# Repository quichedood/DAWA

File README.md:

New version here : https://github.com/quichedood/DAWA-6.1

# DAWA - Data Acquisition With Arduino
French official website project : http://dawa.panik-po.com/

DAWA is an Arduino datalogger (and laptimer) shield for your motorbike.
It records 10 times per seconds in a CSV file lots of information.

# What information is logged ?
* __Raw data acquisition__ : On Triumph bikes and many others, ECU values can be directly read (I personnaly use : RPM, SPEED, GEAR POSITION, THROTTLE and BRAKE state)
* __Environement values__ : A 9-axis sensor (BNO055) is used to store G-forces and I hope soon, roll and pitch
* __Position values__ : A UBLOX 10Hz GPS chip gets realtime coordinates
* __Infrared temperatures__ : You can plug up to 4 infrared temperature sensors (tyres or ground t° for example)
* __Analog inputs__ : You can measure up to 6 analog inputs (suspension sensors for exemple)

# Where is it logged ?
Everything is stored on a micro SD card.  
10 times per seconds, a new line is created in a CSV file. This line contains every data values separated by a semicolon.  
Current values are displayed in realtime on the OLED screen attached.

# Could it be used as a laptimer ?
YES ! Since v4 and the integration of a 10Hz GPS chip, laptimer functions are available.

# How does it work ?
I couldn't make it easier !  
Press the button start recording, press again stop recording :)  
One CSV file is created on each new record.

# What about laptimer functions
A little bit more difficult, you have to put a file named "TRACKS.CSV" on the sdcard.  
This file will contain track name and finishline coordinates, one line per track :  
`<trackname>;<finishline lat. A>;<finishline lon. A>;<finishline lat. B>;<finishline lon. B>`  
`CAROLE;489799930;25224350;489800230;25226330`  
To keep precision, latitude and longitude should be converted to integers (multiply by 10 000 000).  
When start recording the closer track is automatically chosen.

# You said Bluetooth ?
Bluetooth connection is usefull in these 2 cases :
- You just finish your track session and want to know lap times / best lap
- Before using DAWA, some parameters could be adjusted, use the bluetooth console to setup them !

I'm using "Serial Bluetooth Terminal" on Androïd. Connect and type "help" to view all available commands

# What's next  
* __Laptimer split time__ : Add split time management

# Known bugs
* __Lean angle__ : Seems easy but in fact very complicated to obtain good values without drift

# Repository Contents
* /Arduino - The .ino file you need to put in the Arduino M0
* /Documentation - Some brief explanations about this shield (french - not translated)
* /Eagle Libraries - All Eagle parts I use in my schematics
* /Eagle Sources - Eagle files of this project
* /Gerber Sources - Last Gerber files, used to produce PCB
* /Partslist - A detailed BOM list

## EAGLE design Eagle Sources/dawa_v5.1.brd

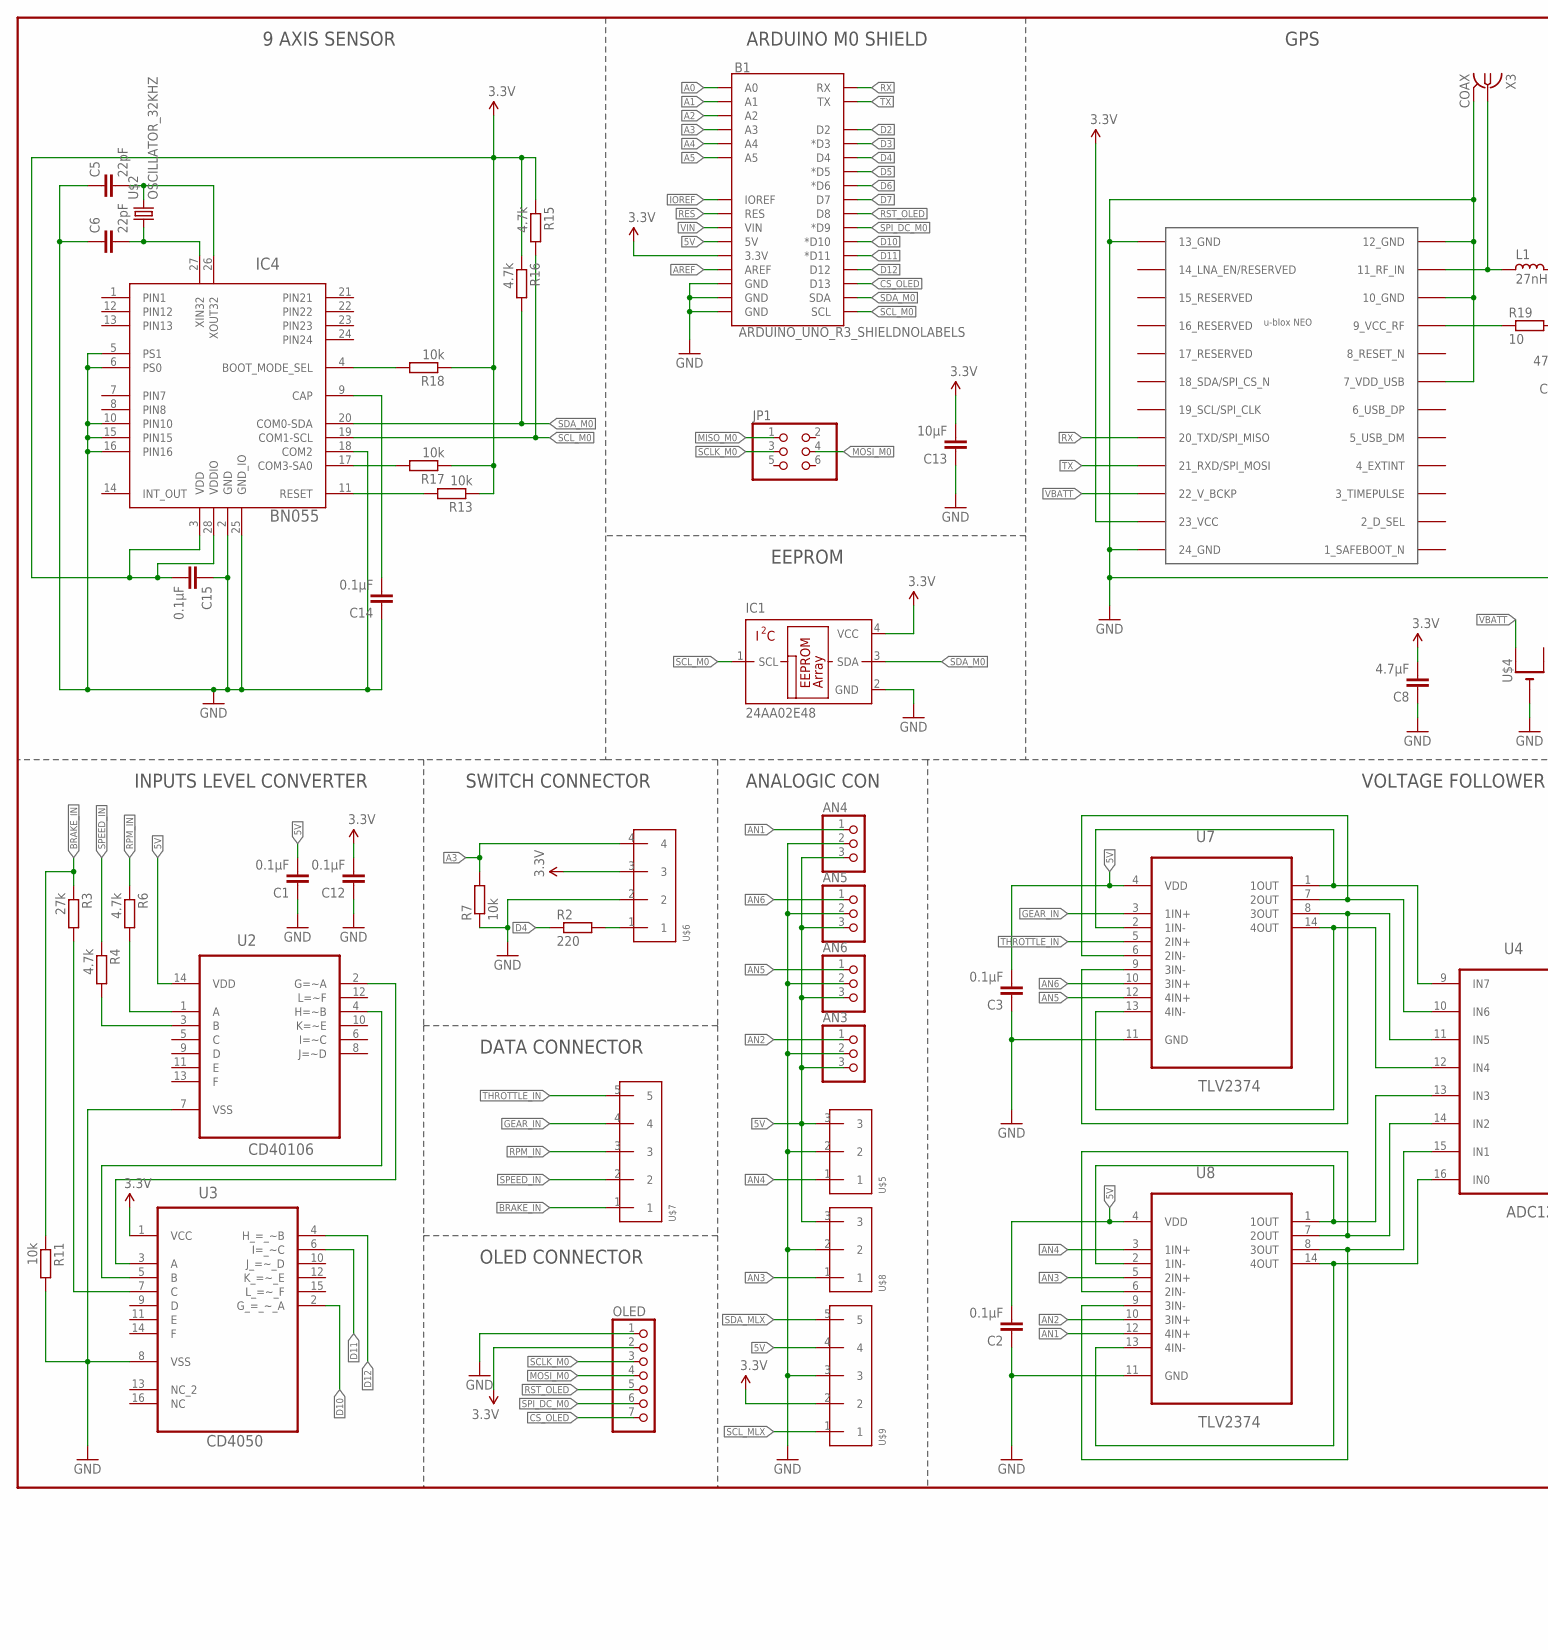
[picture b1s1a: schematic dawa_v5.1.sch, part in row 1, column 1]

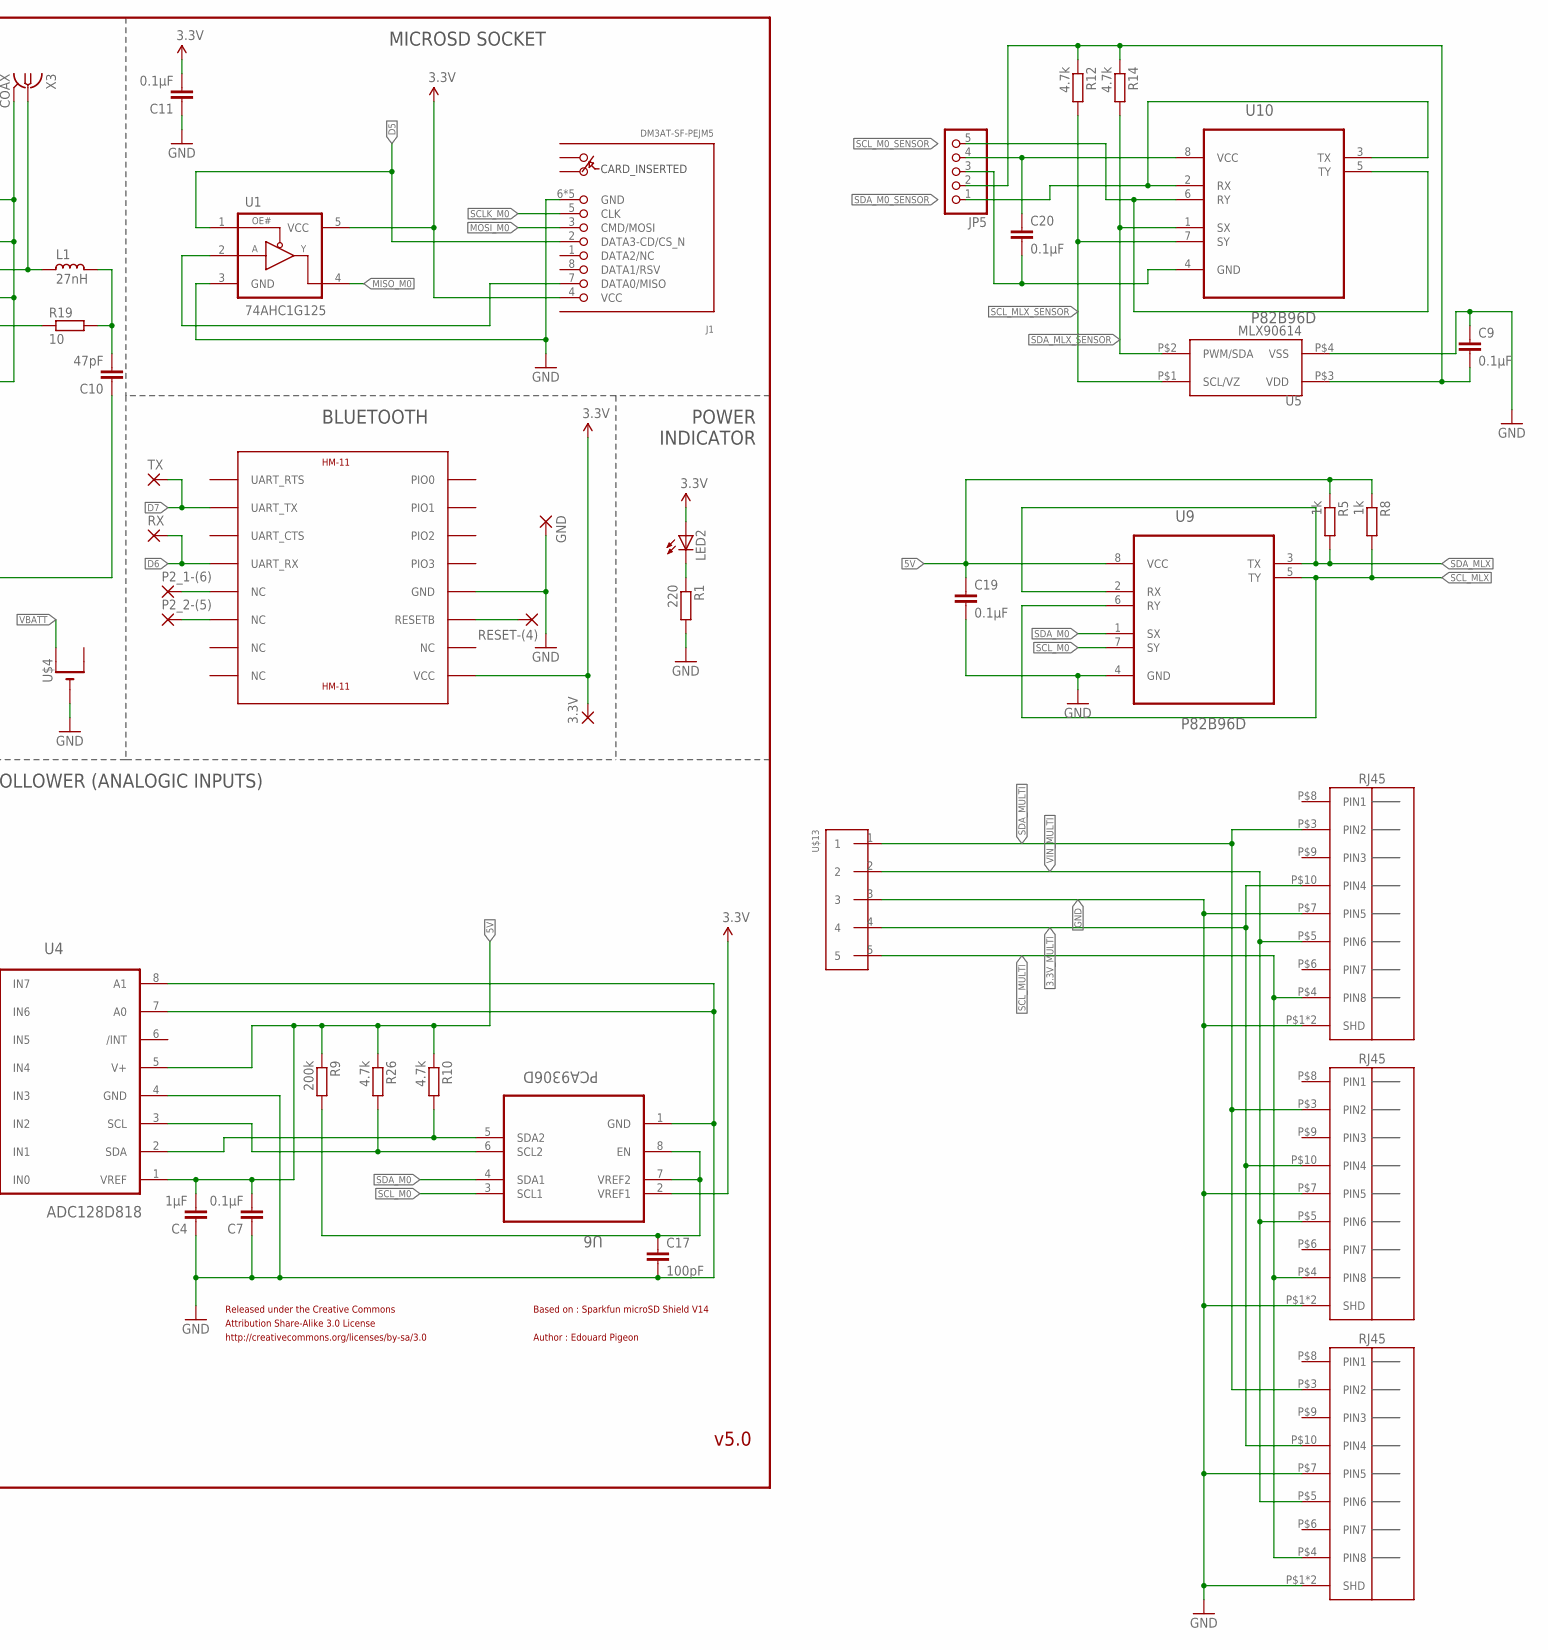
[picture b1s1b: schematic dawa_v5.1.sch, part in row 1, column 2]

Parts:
3.3V: WIREPADSMD1,27-254; SMD1,27-2,54
AN3, AN4, AN5, AN6: PINHD-1X3; 1X03
B1: ARDUINO_UNO_R3_SHIELDNOLABELS; UNO_R3_SHIELD_NOLABELS
C1, C2, C3, C7, C9, C11, C12, C14, C15, C19, C20: 0.1µF; C0603
C4: 1µF; C0603
C5, C6: 22pF; C0603
C8: 4.7µF; C0603
C10: 47pF; C0603
C13: 10µF; C0603
C17: 100pF; C0603
GND: WIREPADSMD1,27-254; SMD1,27-2,54
IC1: 24AA02E48; SOT23-5L
IC4: BN055; LGA-28_3.80X5.20/0.5
J1: DM3AT-SF-PEJM5
JP1: PINHD-2X3; 2X03
JP5: PINHD-1X5; 1X05
L1: 27nH; L0603
LED2: LEDCHIPLED_1206; CHIPLED_1206
OLED: PINHD-1X7; 1X07
P2_1-(6), P2_2-(5): WIREPADSMD1,27-254; SMD1,27-2,54
R1, R2: 220; R0603
R3: 27k; R0603
R4, R6, R10, R12, R14, R15, R16, R26: 4.7k; R0603
R5, R8: 1k; R0603
R7, R11, R13, R17, R18: 10k; R0603
R9: 200k; R0603
R19: 10; M1206
RESET-(4): WIREPADSMD1,27-254; SMD1,27-2,54
RX: WIREPADSMD1,27-254; SMD1,27-2,54
TX: WIREPADSMD1,27-254; SMD1,27-2,54
U1: 74AHC1G125; SOT23-5
U2: CD40106; SOP65P640X120-14N
U3: CD4050; SOP65P640X120-16N
U4: ADC128D818; SOP65P640X120-16N
U5: MLX90614; TO-39
U6: PCA9306D; SOP50P310X90-8N
U7, U8: TLV2374; SOP65P640X120-14N
U9, U10: P82B96D; SOIC127P600X175-8N
U$1: HM-11
U$2: OSCILLATOR_32KHZ; OSCILLATOR_SMD
U$3: NEO-M8
U$4: CR1220SMT; CR1220-SMD
U$5, U$8: 3_PIN_JST-XH-SMD
U$6: 4_PIN_JST-XH-SMD
U$7, U$9, U$13: 5_PIN_JST-XH-SMD
U$10, U$11, U$12: RJ45
X3: COAX; MMCX-J-P-X-ST-EM1-MKT

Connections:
3.3V: 3.3V.1, B1.3.3V, C8.2, C11.2, C12.2, C13.2, C15.2, IC1.4 (VCC), IC4.3 (VDD), IC4.28 (VDDIO), J1.4 (VCC), LED2.A, OLED.2, R13.1, R15.1, R16.1, R17.1, R18.1, U1.5 (VCC), U3.1 (VCC), U6.2 (VREF1), U$1.VCC, U$3.23 (23_VCC), U$6.3, U$9.2
3.3V_MULTI: U$10.P$10 (PIN4), U$11.P$10 (PIN4), U$12.P$10 (PIN4), U$13.4
5V: AN3.3, AN4.3, AN5.3, AN6.3, B1.5V, C1.2, C2.2, C3.2, C4.2, C7.2, C19.1, R5.1, R8.1, R9.1, R10.1, R26.1, U2.14 (VDD), U4.1 (VREF), U4.5 (V+), U7.4 (VDD), U8.4 (VDD), U9.8 (VCC), U$5.3, U$8.3, U$9.4
A0: B1.A0
A1: B1.A1
A2: B1.A2
A3: B1.A3, R7.2, U$6.4
A4: B1.A4
A5: B1.A5
AN1: AN4.1, U8.12 (4IN+)
AN2: AN3.1, U8.10 (3IN+)
AN3: U8.5 (2IN+), U$8.1
AN4: U8.3 (1IN+), U$5.1
AN5: AN6.1, U7.12 (4IN+)
AN6: AN5.1, U7.10 (3IN+)
AREF: B1.AREF
BRAKE_IN: R3.1, R11.1, U$7.1
CS_OLED: B1.D13, OLED.7
D2: B1.D2
D3: B1.D3 (*D3)
D4: B1.D4, R2.1
D5: B1.D5 (*D5), J1.2 (DATA3-CD/CS_N), U1.1 (OE#)
D6: B1.D6 (*D6), RX.1, U$1.UART_RX
D7: B1.D7, TX.1, U$1.UART_TX
D10: B1.D10 (*D10), U3.2 (G_=_~_A)
D11: B1.D11 (*D11), U3.6 (I=_~C)
D12: B1.D12, U3.4 (H_=_~B)
GEAR_IN: U7.3 (1IN+), U$7.4
GND: AN3.2, AN4.2, AN5.2, AN6.2, B1.GND@0 (GND), B1.GND@1 (GND), B1.GND@2 (GND), C1.1, C2.1, C3.1, C4.1, C5.1, C6.1, C7.1, C8.1, C9.1, C10.1, C11.1, C12.1, C13.1, C14.1, C15.1, C17.2, C19.2, GND.1, IC1.2 (GND), IC4.2 (GND), IC4.5 (PS1), IC4.6 (PS0), IC4.10 (PIN10), IC4.15 (PIN15), IC4.16 (PIN16), IC4.18 (COM2), IC4.25 (GND_IO), J1.6 (GND), J1.MOUNT0 (GND), J1.MOUNT1 (GND), J1.MOUNT2 (GND), J1.MOUNT3 (GND), OLED.1, R1.2, R7.1, R11.2, U1.3 (GND), U2.7 (VSS), U3.8 (VSS), U4.4 (GND), U4.7 (A0), U4.8 (A1), U5.P$4 (VSS), U6.1 (GND), U7.11 (GND), U8.11 (GND), U9.4 (GND), U$1.GND, U$3.7 (7_VDD_USB), U$3.10 (10_GND), U$3.12 (12_GND), U$3.13 (13_GND), U$3.24 (24_GND), U$4.-, U$5.2, U$6.2, U$8.2, U$9.3, U$10.P$1 (SHD), U$10.P$2 (SHD), U$10.P$7 (PIN5), U$11.P$1 (SHD), U$11.P$2 (SHD), U$11.P$7 (PIN5), U$12.P$1 (SHD), U$12.P$2 (SHD), U$12.P$7 (PIN5), U$13.3, X3.2@1 (GND), X3.2@2 (GND), X3.2@3 (GND), X3.2@4 (GND)
IOREF: B1.IOREF
MISO_M0: JP1.1, U1.4 (Y)
MOSI_M0: J1.3 (CMD/MOSI), JP1.4, OLED.4
unnamed: R2.2, U$6.1
unnamed: R6.2, U2.1 (A)
unnamed: U2.2 (G=~A), U3.3 (A)
unnamed: R4.2, U2.3 (B)
unnamed: R3.2, U3.7 (C)
unnamed: LED2.C, R1.1
unnamed: IC4.11 (RESET), R13.2
unnamed: P2_1-(6).1, U$1.NC@5 (NC)
unnamed: RESET-(4).1, U$1.RESETB
unnamed: J1.7 (DATA0/MISO), U1.2 (A)
unnamed: C10.2, L1.1, R19.2
unnamed: U4.13 (IN3), U8.1 (1OUT), U8.2 (1IN-)
unnamed: C14.2, IC4.9 (CAP)
unnamed: IC4.4 (BOOT_MODE_SEL), R18.2
unnamed: C5.2, IC4.26 (XOUT32), U$2.2
unnamed: C6.2, IC4.27 (XIN32), U$2.1
unnamed: IC4.17 (COM3-SA0), R17.2
unnamed: P2_2-(5).1, U$1.NC@6 (NC)
unnamed: R19.1, U$3.9 (9_VCC_RF)
unnamed: L1.2, U$3.11 (11_RF_IN), X3.1
unnamed: U2.4 (H=~B), U3.5 (B)
unnamed: R26.2, U4.3 (SCL), U6.6 (SCL2)
unnamed: R10.2, U4.2 (SDA), U6.5 (SDA2)
unnamed: U4.9 (IN7), U7.1 (1OUT), U7.2 (1IN-)
unnamed: U4.10 (IN6), U7.6 (2IN-), U7.7 (2OUT)
unnamed: U4.11 (IN5), U7.8 (3OUT), U7.9 (3IN-)
unnamed: U4.12 (IN4), U7.13 (4IN-), U7.14 (4OUT)
unnamed: C17.1, R9.2, U6.7 (VREF2), U6.8 (EN)
unnamed: U4.14 (IN2), U8.6 (2IN-), U8.7 (2OUT)
unnamed: U4.15 (IN1), U8.8 (3OUT), U8.9 (3IN-)
unnamed: U4.16 (IN0), U8.13 (4IN-), U8.14 (4OUT)
unnamed: C20.1, JP5.4, U10.8 (VCC)
unnamed: C9.2, JP5.2, R12.1, R14.1, U5.P$3 (VDD)
unnamed: C20.2, JP5.3, U10.4 (GND)
RES: B1.RES
RPM_IN: R6.1, U$7.3
RST_OLED: B1.D8, OLED.5
RX: B1.RX, U$3.20 (20_TXD/SPI_MISO)
SCLK_M0: J1.5 (CLK), JP1.3, OLED.3
SCL_M0: B1.SCL, IC1.1 (SCL), IC4.19 (COM1-SCL), R15.2, U6.3 (SCL1), U9.7 (SY)
SCL_M0_SENSOR: JP5.5, U10.5 (TY), U10.6 (RY)
SCL_MLX: R8.2, U9.5 (TY), U9.6 (RY), U$9.1
SCL_MLX_SENSOR: R12.2, U5.P$1 (SCL/VZ), U10.7 (SY)
SCL_MULTI: U$10.P$4 (PIN8), U$11.P$4 (PIN8), U$12.P$4 (PIN8), U$13.5
SDA_M0: B1.SDA, IC1.3 (SDA), IC4.20 (COM0-SDA), R16.2, U6.4 (SDA1), U9.1 (SX)
SDA_M0_SENSOR: JP5.1, U10.2 (RX), U10.3 (TX)
SDA_MLX: R5.2, U9.2 (RX), U9.3 (TX), U$9.5
SDA_MLX_SENSOR: R14.2, U5.P$2 (PWM/SDA), U10.1 (SX)
SDA_MULTI: U$10.P$3 (PIN2), U$11.P$3 (PIN2), U$12.P$3 (PIN2), U$13.1
SPEED_IN: R4.1, U$7.2
SPI_DC_M0: B1.D9 (*D9), OLED.6
THROTTLE_IN: U7.5 (2IN+), U$7.5
TX: B1.TX, U$3.21 (21_RXD/SPI_MOSI)
VBATT: U$3.22 (22_V_BCKP), U$4.+$1 (+)
VIN: B1.VIN
VIN_MULTI: U$10.P$5 (PIN6), U$11.P$5 (PIN6), U$12.P$5 (PIN6), U$13.2

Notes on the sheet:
POWER INDICATOR
Released under the Creative Commons
v5.0
VOLTAGE FOLLOWER (ANALOGIC INPUTS)
MICROSD SOCKET
ARDUINO M0 SHIELD
BLUETOOTH
Attribution Share-Alike 3.0 License
http://creativecommons.org/licenses/by-sa/3.0
Based on : Sparkfun microSD Shield V14
Author : Edouard Pigeon
9 AXIS SENSOR
INPUTS LEVEL CONVERTER
OLED CONNECTOR
DATA CONNECTOR
EEPROM
SWITCH CONNECTOR
GPS
ANALOGIC CON

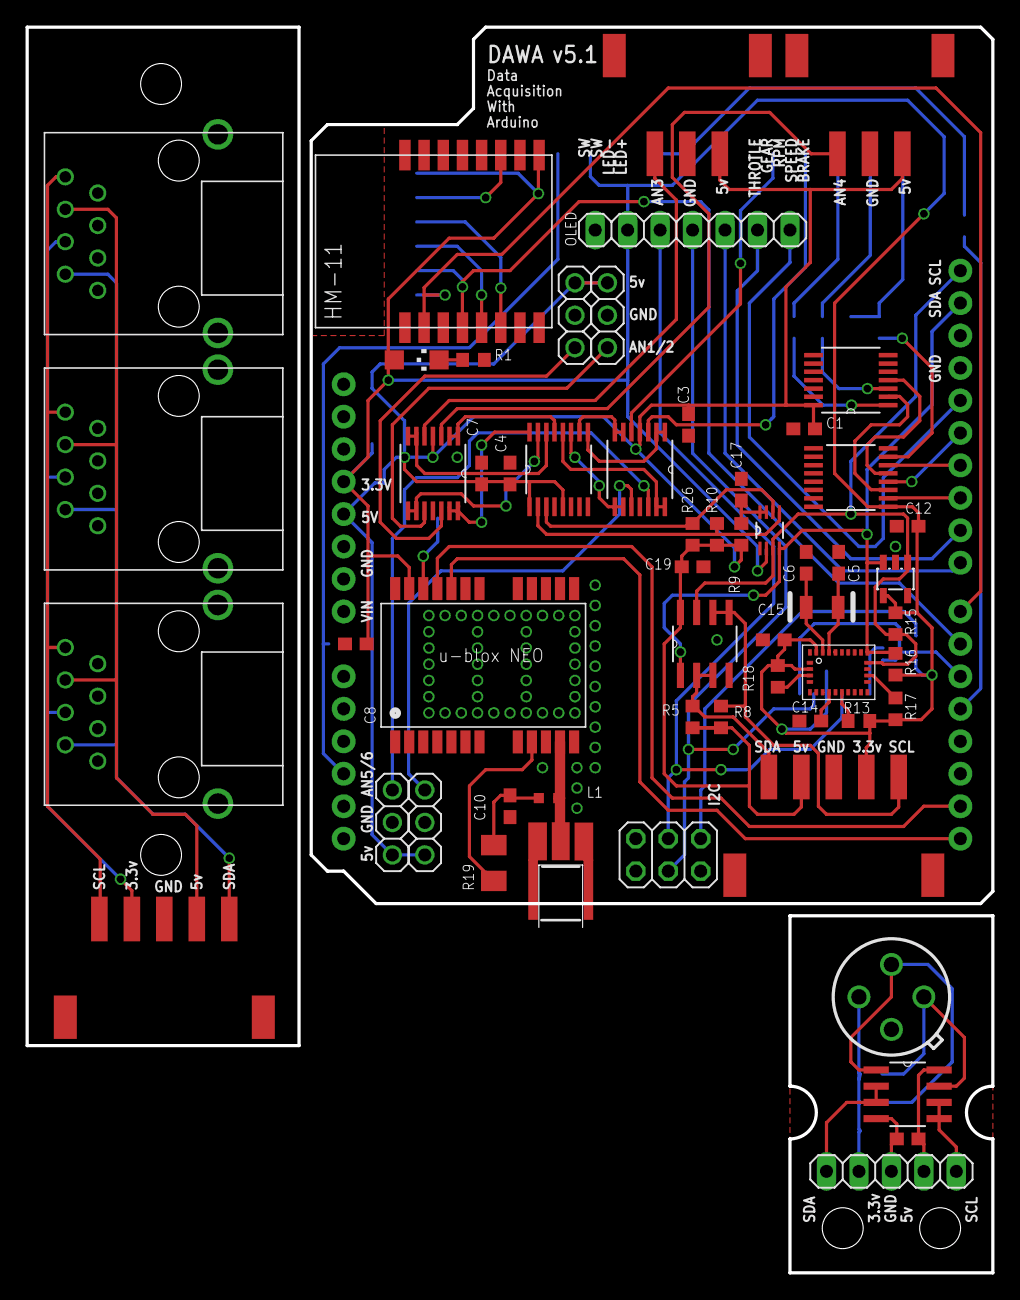
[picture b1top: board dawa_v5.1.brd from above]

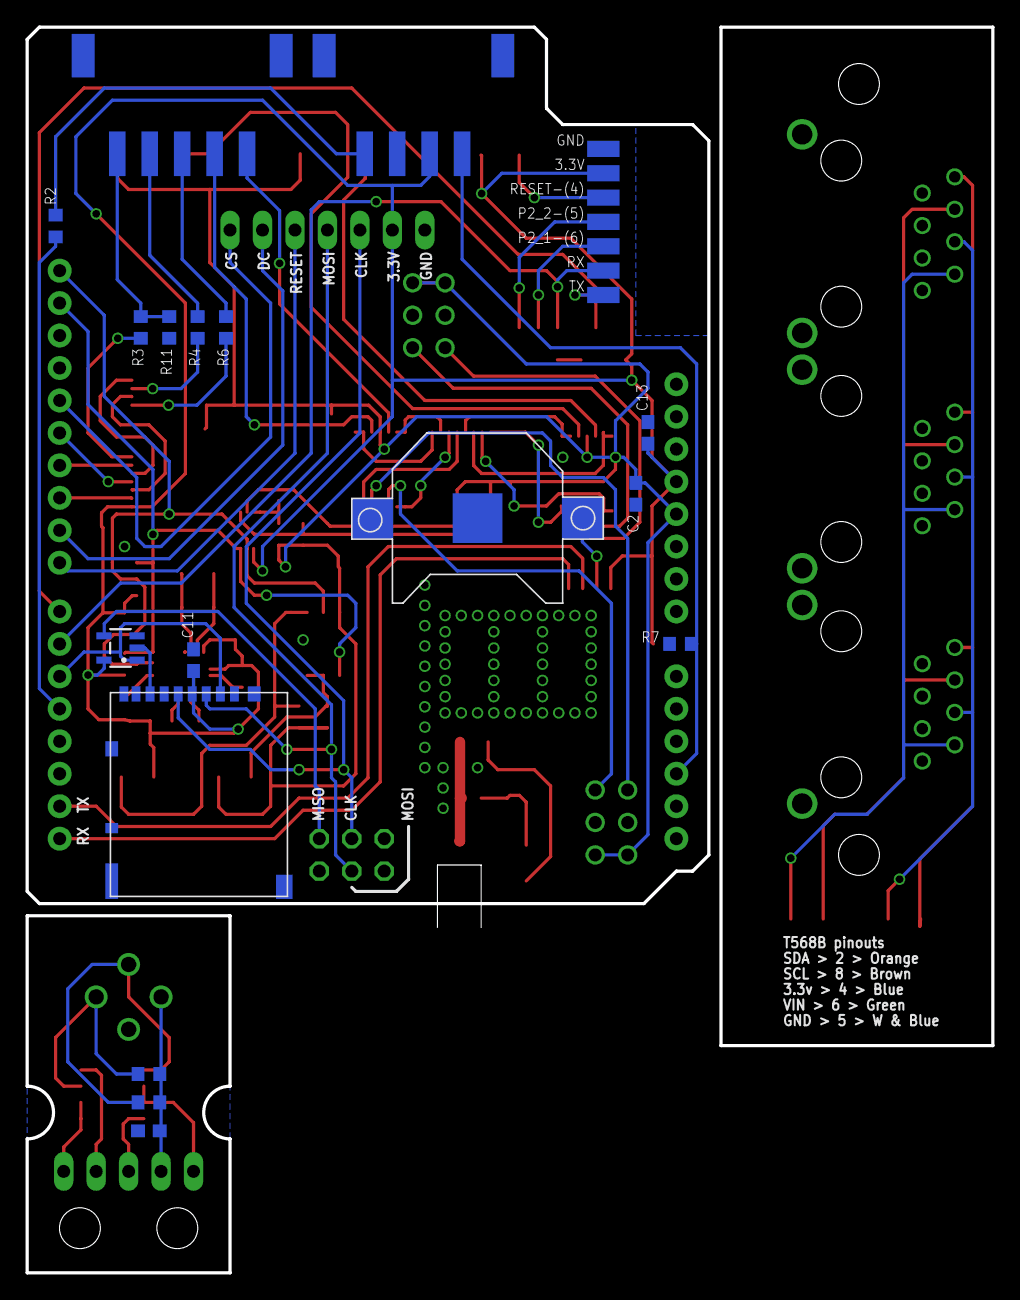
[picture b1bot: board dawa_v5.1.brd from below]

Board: 2 copper layers, 75.6 x 97.5 mm, 82 parts (24 on the bottom side), 77 nets.

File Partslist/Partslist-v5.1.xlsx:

Qty | Retailer | Value | Ref | Device | Package
1 | Mouser |  | CR1220 | 12mm 3V lithium coin cell
1 | Aliexpress |  |  | 12v connector
1 | Mouser |  | ADC128D818 | ADC | SOP65P640X120-16N
1 | Aliexpress |  |  | Arduino M0 (Robodyn)
1 | Aliexpress | 100pF |  | Capacitor | 0603
1 | Aliexpress | 10µF |  | Capacitor | 0603
1 | Aliexpress | 1µF |  | Capacitor | 0603
1 | Aliexpress | 4.7µF |  | Capacitor | 0603
2 | Aliexpress | 22pF |  | Capacitor | 0603
11 | Aliexpress | 0.1µF |  | Capacitor | 0603
1 | Mouser | 47pF | GRM1885C1H470JA01D | Capacitor | 0603
1 | Aliexpress |  | CD4050 | CMOS Hex Buffer/Converters | SOP65P640X120-16N
3 | Aliexpress |  | P82B96D | DUAL BIDIRECTIONAL BUS BUFFER | SOIC127P600X175-8N
1 | Aliexpress |  |  | GPS Antenna
1 | Aliexpress |  |  | GPS connector | MMCX STRAIGHT, EDGE MOUNT JACK- 50 OHM
1 | Aliexpress |  | UBLOX NEO-7M | GPS module
1 | Aliexpress |  |  | HM-11 (Bluetooth module) | JNHuaMao HM-11 Bluetooth 4.0 Transceiver
1 | Mouser | 27nH | LQG18HN27NJ00D | Inductor | 0603
2 | Aliexpress |  | MLX90614 ESF-BCC | Infrared temp. Sensor
1 | Mouser |  | BN055 | Intelligent 9-axis absolute orientation sensor | LGA-28_3.80X5.20/0.5
2 | Aliexpress |  |  | JST XH Connector (3 pins/F)
1 | Aliexpress |  |  | JST XH Connector (4 pins/F)
3 | Aliexpress |  |  | JST XH Connector (5 pins/F)
2 | Aliexpress |  |  | JST XH Connector (SMD/3 pins/M)
1 | Aliexpress |  |  | JST XH Connector (SMD/4 pins/M)
3 | Aliexpress |  |  | JST XH Connector (SMD/5 pins/M)
1 | Aliexpress |  |  | LED | 1206
1 | Aliexpress |  |  | Lithium coin cell 3v
1 | Aliexpress |  | DM3AT-SF-PEJM5 | Micro SD connector (SMD/push/push) | DM3AT-SF-PEJM5
1 | Aliexpress |  |  | OLED screen
2 | Mouser |  | TLV2374IPWR | OPERATIONAL AMPLIFIERS | SOP65P640X120-14N
1 | Mouser | 32.768kHz | CM7V-T1A | OSCILLATOR
1 | N/A |  |  | PCB
1 | Aliexpress |  |  | Pin header 1X32 (M)
1 | Mouser |  |  | Pin header 1X7 (F)
1 | Aliexpress |  |  | Pin header 2X3 (F)
1 | Aliexpress |  |  | Power button
1 | Mouser |  | CD40106BPW | QUADRUPLE LEVEL SHIFTER | SOP65P640X120-14N
1 | Aliexpress | 1kohm |  | Resistor | 0603
1 | Aliexpress | 200kohm |  | Resistor | 0603
1 | Aliexpress | 27kohm |  | Resistor | 0603
2 | Aliexpress | 220ohm |  | Resistor | 0603
8 | Aliexpress | 4.7kohm |  | Resistor | 0603
5 | Aliexpress | 10kohm |  | Resistor | 0603
1 | Mouser | 10ohm |  | Resistor | 1206
2 | Amazon |  |  | RJ45 (1m/2m)
3 | Aliexpress |  |  | RJ45 female socket
1 | Mouser |  | 24AA02E48 | Serial EEPROM | SOT23-5L
1 | Mouser |  | 74AHC1G125 | TRI-STATE SINGLE BUSS BUFFER | SOT23-5
1 | Mouser |  | PCA9306D | VOLTAGE-LEVEL TRANSLATOR | SOP50P310X90-8N
2 | Aliexpress |  |  | Wire cable (2m) - 4 cores
2 | Aliexpress |  |  | Wire cable (2m) - 5 cores

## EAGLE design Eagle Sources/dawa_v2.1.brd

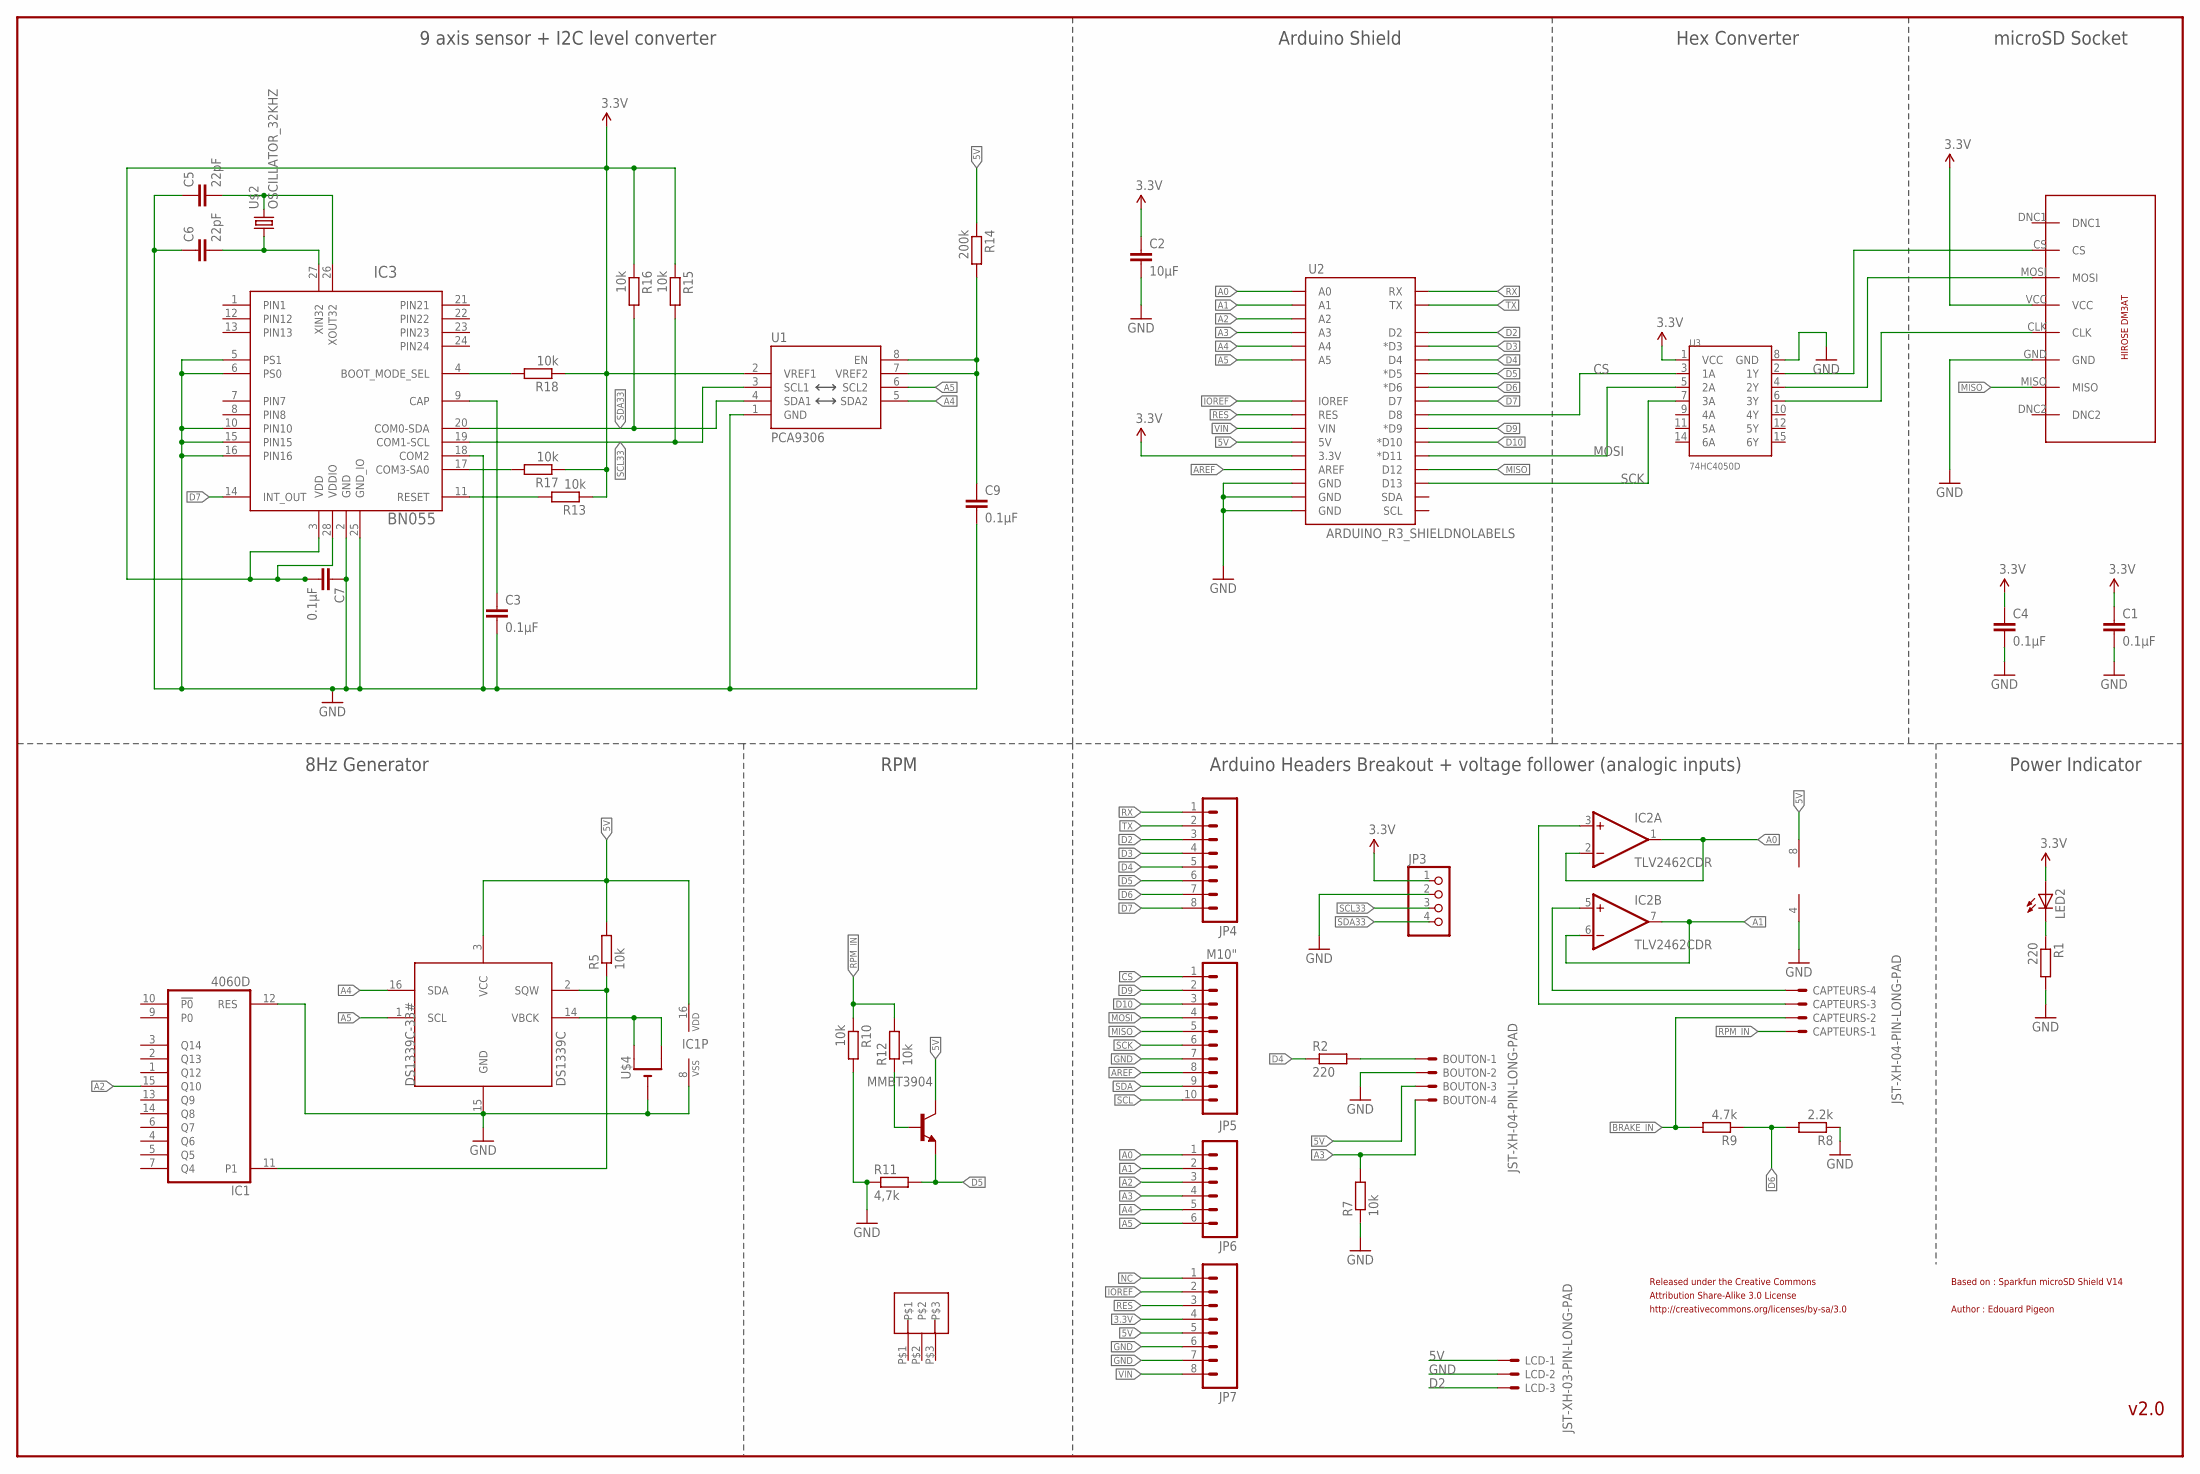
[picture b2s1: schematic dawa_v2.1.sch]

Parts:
BOUTON: JST-XH-04-PIN-LONG-PAD; JST-XH-04-PACKAGE-LONG-PAD
C1, C3, C4, C7, C9: 0.1µF; C1206
C2: 10µF; C1206
C5, C6: 22pF; C1206
CAPTEURS: JST-XH-04-PIN-LONG-PAD; JST-XH-04-PACKAGE-LONG-PAD
DS1339C-33#: DS1339C
IC1: 4060D; SO16
IC2: TLV2462CDR; SO08
IC3: BN055; LGA-28_3.80X5.20/0.5
JP3: PINHD-1X4; 1X04
JP4: M08; 1X08
JP5: M10"; 1X10
JP6: M06SIP; 1X06
JP7: M081X08; 1X08
LCD: JST-XH-03-PIN-LONG-PAD; JST-XH-03-PACKAGE-LONG-PAD
LED2: LEDCHIPLED_1206; CHIPLED_1206
MMBT3904: MMBT3904LT1-NPN-SOT23-BEC; SOT23-BEC
R1, R2: 220; M1206
R5, R7, R10, R12, R13, R15, R16, R17, R18: 10k; M1206
R8: 2.2k; M1206
R9: 4.7k; M1206
R11: 4,7k; M1206
R14: 200k; M1206
U1: PCA9306; PSOP-8
U2: ARDUINO_R3_SHIELDNOLABELS; UNO_R3_SHIELD_NOLABELS
U3: 74HC4050D; SO016
U$2: OSCILLATOR_32KHZ; OSCILLATOR_SMD
U$3: 3_PIN_JST-XH
U$4: CR1220SMT; CR1220-SMD
U$5: DM3AT

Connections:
3.3V: C1.1, C2.1, C4.1, C7.2, IC3.3 (VDD), IC3.28 (VDDIO), JP3.1, JP7.4, LED2.A, R13.1, R15.1, R16.1, R17.1, R18.1, U1.2 (VREF1), U2.3.3V, U3.1 (VCC), U$5.VCC
5V: BOUTON.3, DS1339C-33#.3 (VCC), IC1.16 (VDD), IC2.8 (V+), JP7.5, LCD.1, MMBT3904.C, R5.2, R14.1, U2.5V
A0: IC2.1 (OUT), IC2.2 (-IN), JP6.1, U2.A0
A1: IC2.6 (-IN), IC2.7 (OUT), JP6.2, U2.A1
A2: IC1.15 (Q10), JP6.3, U2.A2
A3: BOUTON.4, JP6.4, R7.2, U2.A3
A4: DS1339C-33#.16 (SDA), JP6.5, U1.5 (SDA2), U2.A4
A5: DS1339C-33#.1 (SCL), JP6.6, U1.6 (SCL2), U2.A5
AREF: JP5.8, U2.AREF
BRAKE_IN: CAPTEURS.2, R9.2
CS: JP5.1, U2.D8, U3.3 (1A)
D2: JP4.3, LCD.3, U2.D2
D3: JP4.4, U2.D3 (*D3)
D4: JP4.5, R2.1, U2.D4
D5: JP4.6, MMBT3904.E, R11.2, U2.D5 (*D5)
D6: JP4.7, R8.2, R9.1, U2.D6 (*D6)
D7: IC3.14 (INT_OUT), JP4.8, U2.D7
D9: JP5.2, U2.D9 (*D9)
D10: JP5.3, U2.D10 (*D10)
GND: BOUTON.2, C1.2, C2.2, C3.2, C4.2, C5.1, C6.1, C7.1, C9.2, DS1339C-33#.15 (GND), IC1.8 (VSS), IC1.12 (RES), IC2.4 (V-), IC3.2 (GND), IC3.5 (PS1), IC3.6 (PS0), IC3.10 (PIN10), IC3.15 (PIN15), IC3.16 (PIN16), IC3.18 (COM2), IC3.25 (GND_IO), JP3.2, JP5.7, JP7.6, JP7.7, LCD.2, R1.2, R7.1, R8.1, R10.2, R11.1, U1.1 (GND), U2.GND@0 (GND), U2.GND@1 (GND), U2.GND@2 (GND), U3.8 (GND), U$4.-, U$5.GND
IOREF: JP7.2, U2.IOREF
MISO: JP5.5, U2.D12, U$5.MISO
MOSI: JP5.4, U2.D11 (*D11), U3.5 (2A)
unnamed: BOUTON.1, R2.2
unnamed: U3.4 (2Y), U$5.MOSI
unnamed: DS1339C-33#.14 (VBCK), U$4.+$1 (+), U$4.+$2 (+1)
unnamed: U3.6 (3Y), U$5.CLK
unnamed: LED2.C, R1.1
unnamed: IC3.11 (RESET), R13.2
unnamed: CAPTEURS.4, IC2.5 (+IN)
unnamed: CAPTEURS.3, IC2.3 (+IN)
unnamed: C9.1, R14.2, U1.7 (VREF2), U1.8 (EN)
unnamed: C3.1, IC3.9 (CAP)
unnamed: IC3.4 (BOOT_MODE_SEL), R18.2
unnamed: C5.2, IC3.26 (XOUT32), U$2.2
unnamed: C6.2, IC3.27 (XIN32), U$2.1
unnamed: IC3.17 (COM3-SA0), R17.2
unnamed: DS1339C-33#.2 (SQW), IC1.11 (P1), R5.1
unnamed: MMBT3904.B, R12.1
unnamed: U3.2 (1Y), U$5.CS
NC: JP7.1
RES: JP7.3, U2.RES
RPM_IN: CAPTEURS.1, R10.1, R12.2
RX: JP4.1, U2.RX
SCK: JP5.6, U2.D13, U3.7 (3A)
SCL: JP5.10
SCL33: IC3.19 (COM1-SCL), JP3.3, R15.2, U1.3 (SCL1)
SDA: JP5.9
SDA33: IC3.20 (COM0-SDA), JP3.4, R16.2, U1.4 (SDA1)
TX: JP4.2, U2.TX
VIN: JP7.8, U2.VIN

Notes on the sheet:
Power Indicator
Released under the Creative Commons
v2.0
Arduino Headers Breakout + voltage follower (analogic inputs)
microSD Socket
Hex Converter
Arduino Shield
8Hz Generator
RPM
Attribution Share-Alike 3.0 License
http://creativecommons.org/licenses/by-sa/3.0
Based on : Sparkfun microSD Shield V14
Author : Edouard Pigeon
9 axis sensor + I2C level converter

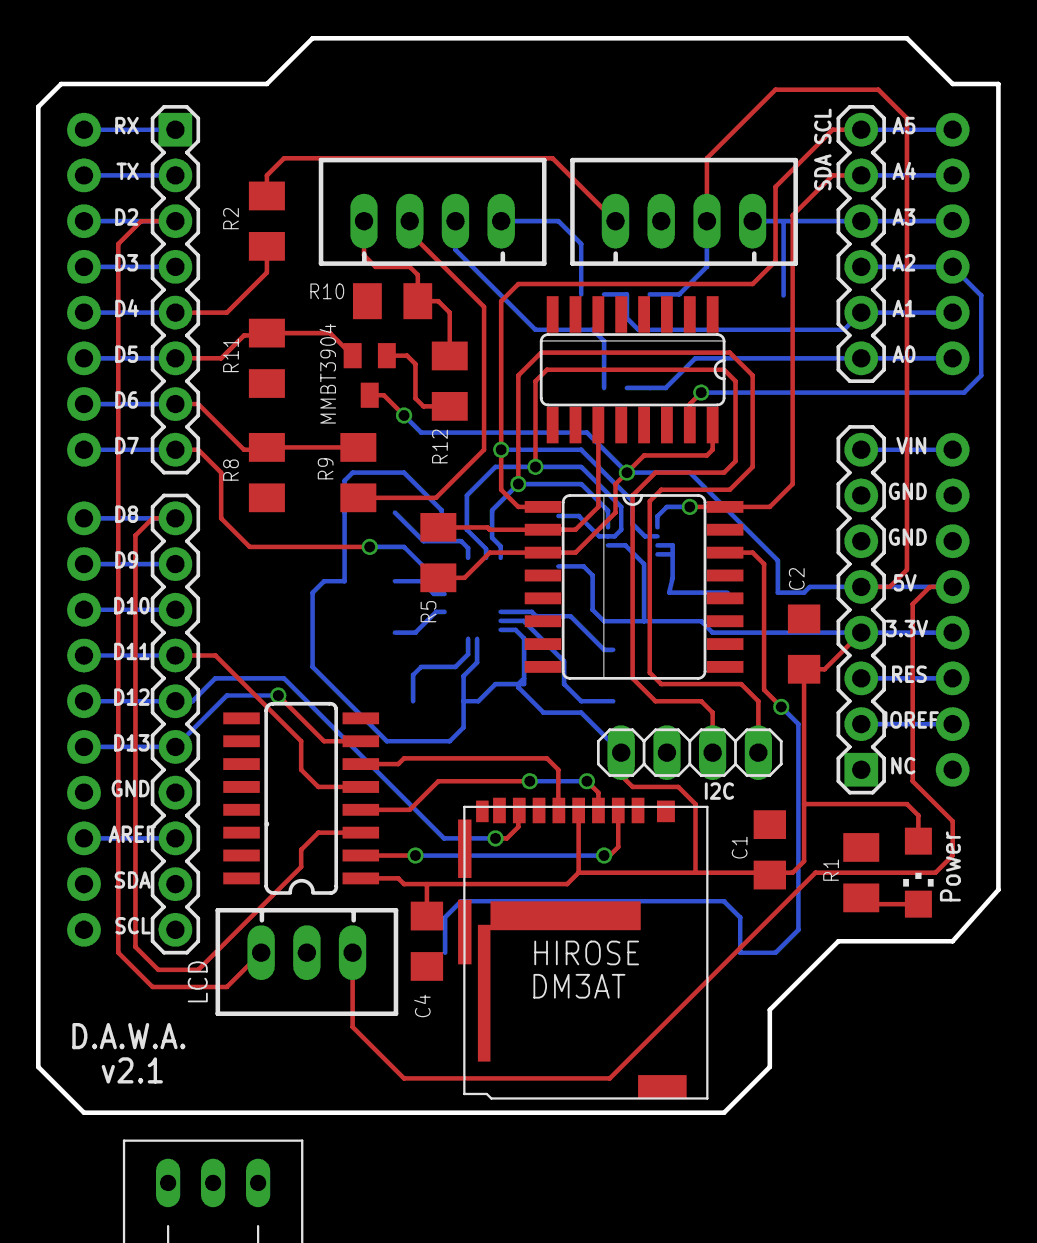
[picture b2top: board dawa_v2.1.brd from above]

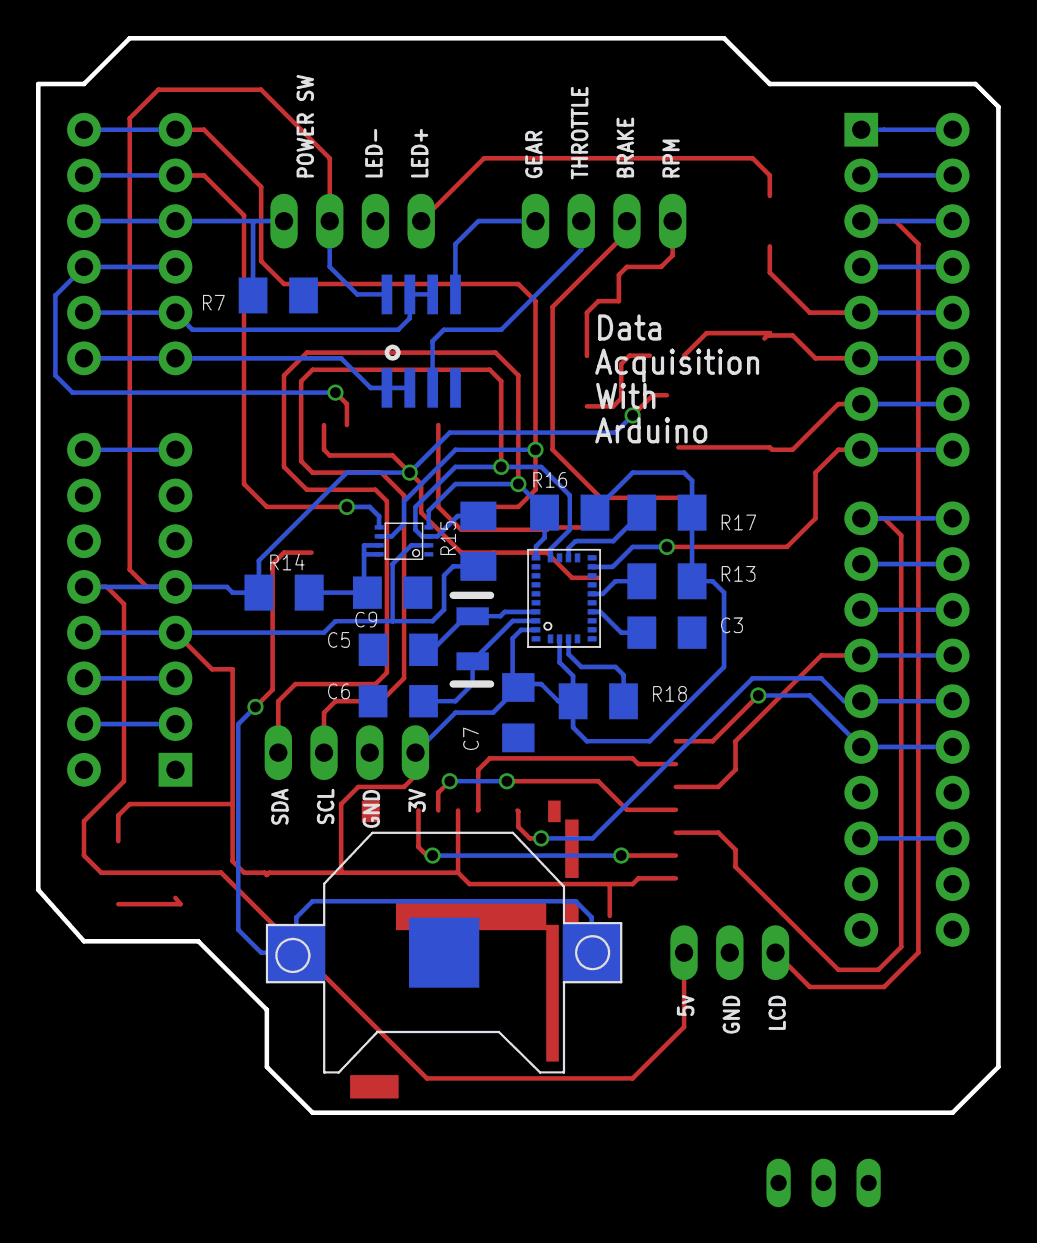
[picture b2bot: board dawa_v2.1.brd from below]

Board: 2 copper layers, 53.3 x 59.7 mm, 44 parts (17 on the bottom side), 48 nets.

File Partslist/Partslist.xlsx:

Qté | Revendeur | Valeur | Produit | Package | Description
1 | Aliexpress |  |  |  | Connecteur 12v DC
1 | Aliexpress |  |  |  | Boitier Plexi
1 | Aliexpress |  |  |  | Bouton LED 16mm
1 | Aliexpress |  |  |  | Arduino UNO
2 | Aliexpress |  |  |  | Fil electrique (2m)
1 | Ebay | 2.2k | R-EU_M1206 | 1206 | Résistance
1 | Ebay | 200k | R-EU_M1206 | 1206 | Résistance
2 | Ebay | 220 | R-EU_M1206 | 1206 | Résistance
2 | Ebay | 4,7k | R-EU_M1206 | 1206 | Résistance
9 | Ebay | 10k | R-EU_M1206 | 1206 | Résistance
1 | Elecrow |  |  |  | Circuit imprimé
1 | Mouser | 32768Hz | LFXTAL009678 |  | Quartz 32.768 kHz
2 | Mouser |  | PINHD-1X16 |  | PIN HEADER
2 | Mouser | 22pF | C-EUC1206 | 1206 | Condensateur
1 | Mouser |  | 74HC4050D | SO016 | HEX CONVERTER
1 | Mouser | 10µF | C-EUC1206 | 1206 | Condensateur
1 | Mouser |  | MMBT3904LT1-NPN | SOT23-BEC | Transistor NPN
1 | Mouser |  | LEDCHIPLED_1206 | 1206 | LED
5 | Mouser | 0.1µF | C-EUC1206 | 1206 | Condensateur
1 | Mouser |  | 74HC4060D | SO16 | 14-stage binary/ripple COUNTER
1 | Mouser |  | TLV2462CDR | SO08 | OP AMP
1 | Mouser |  | PCA9306DC1 | PSOP-8 | Bidirectional I2C level shifter
1 | Mouser |  | DM3AT-SF-PEJM526 |  | Memory Card Connectors SD R/A PUSH-PUSH
1 | Mouser |  | DS1339C-33# | DS1339C | Real-Time Clock (RTC)
1 | Mouser |  | BNO055 | LGA-28_3.80X5.20/0.5 | BN055 Intelligent 9-axis absolute orientation sensor
1 | Mouser |  |  |  | Battery holder CR12xx

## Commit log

2017-03-13 :confetti_ball: Added .gitattributes & .gitignore files
2017-03-13 DAWA
    Data Acquisition With Arduino
2017-06-22 Version 2.1
2017-08-16 DAWA v4.0
    DAWA v4.0
2017-08-26 Add laptimer func/bugs
    Add laptimer functionality based on GPS
    Many optimizations (remove temp string vars)
    Bugs correction
2017-08-27 GPS optimizations
    Change serial baudrate for GPS
    Optimizations on sentences sent by GPS (keep RMC and GGA only)
2017-08-29 Update doc
2017-09-18 v4.4
    Add comments + bug correction in lap calculations
2018-02-12 DAWA v5.5
    Add analog inputs
    Add HM-10 bluetooth support
    Add connectors
2018-06-07 DAWA v5.1
    Update DAWA 5.1
2018-06-10 DAWA v5.1
2018-10-11 3D Case
    STL files for case 3D printing
2020-07-06 STL update

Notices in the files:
parts and their libraries:
SparkFun-Boards: Licensing: CC v3.0 Share-Alike You are welcome to use this library for commercial purposes.
SparkFun-DigitalIC: Licensing: Creative Commons ShareAlike 4.0 International - https://creativecommons.org/licenses/by-sa/4.0
74ah: Copyright (C) 2007, Bob Starr
